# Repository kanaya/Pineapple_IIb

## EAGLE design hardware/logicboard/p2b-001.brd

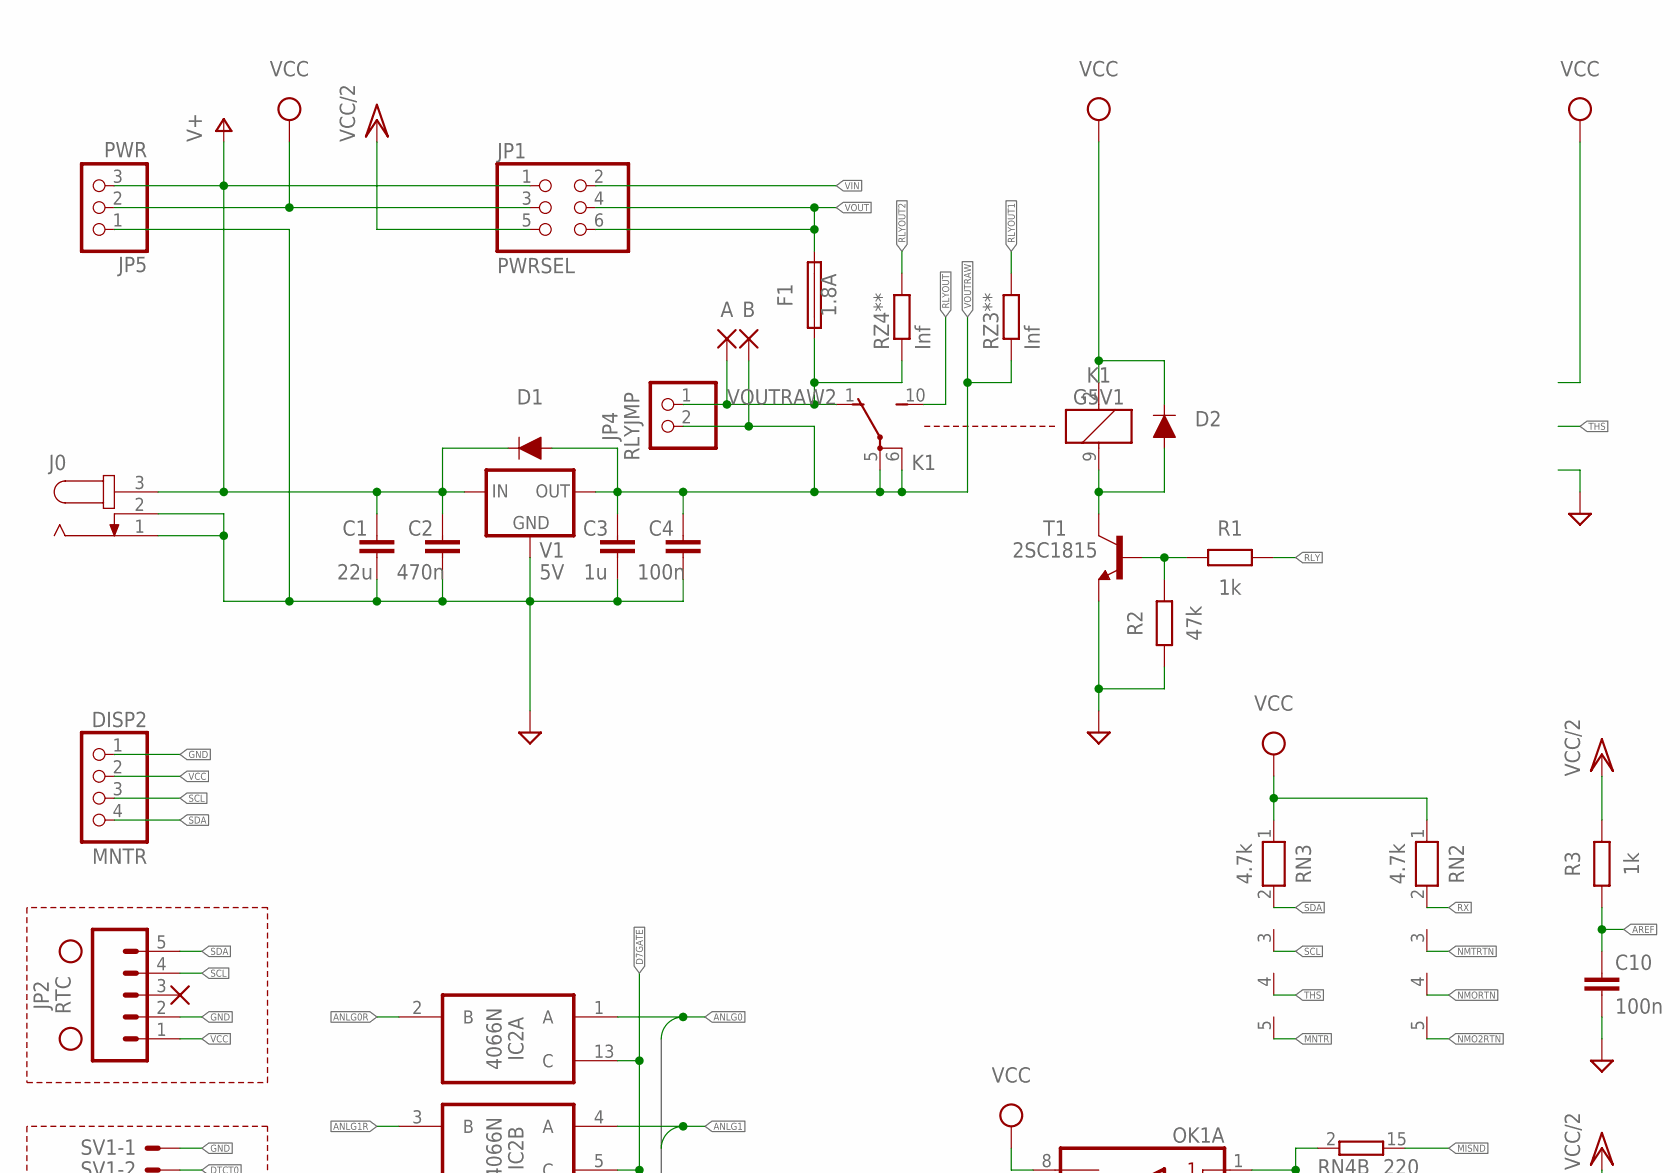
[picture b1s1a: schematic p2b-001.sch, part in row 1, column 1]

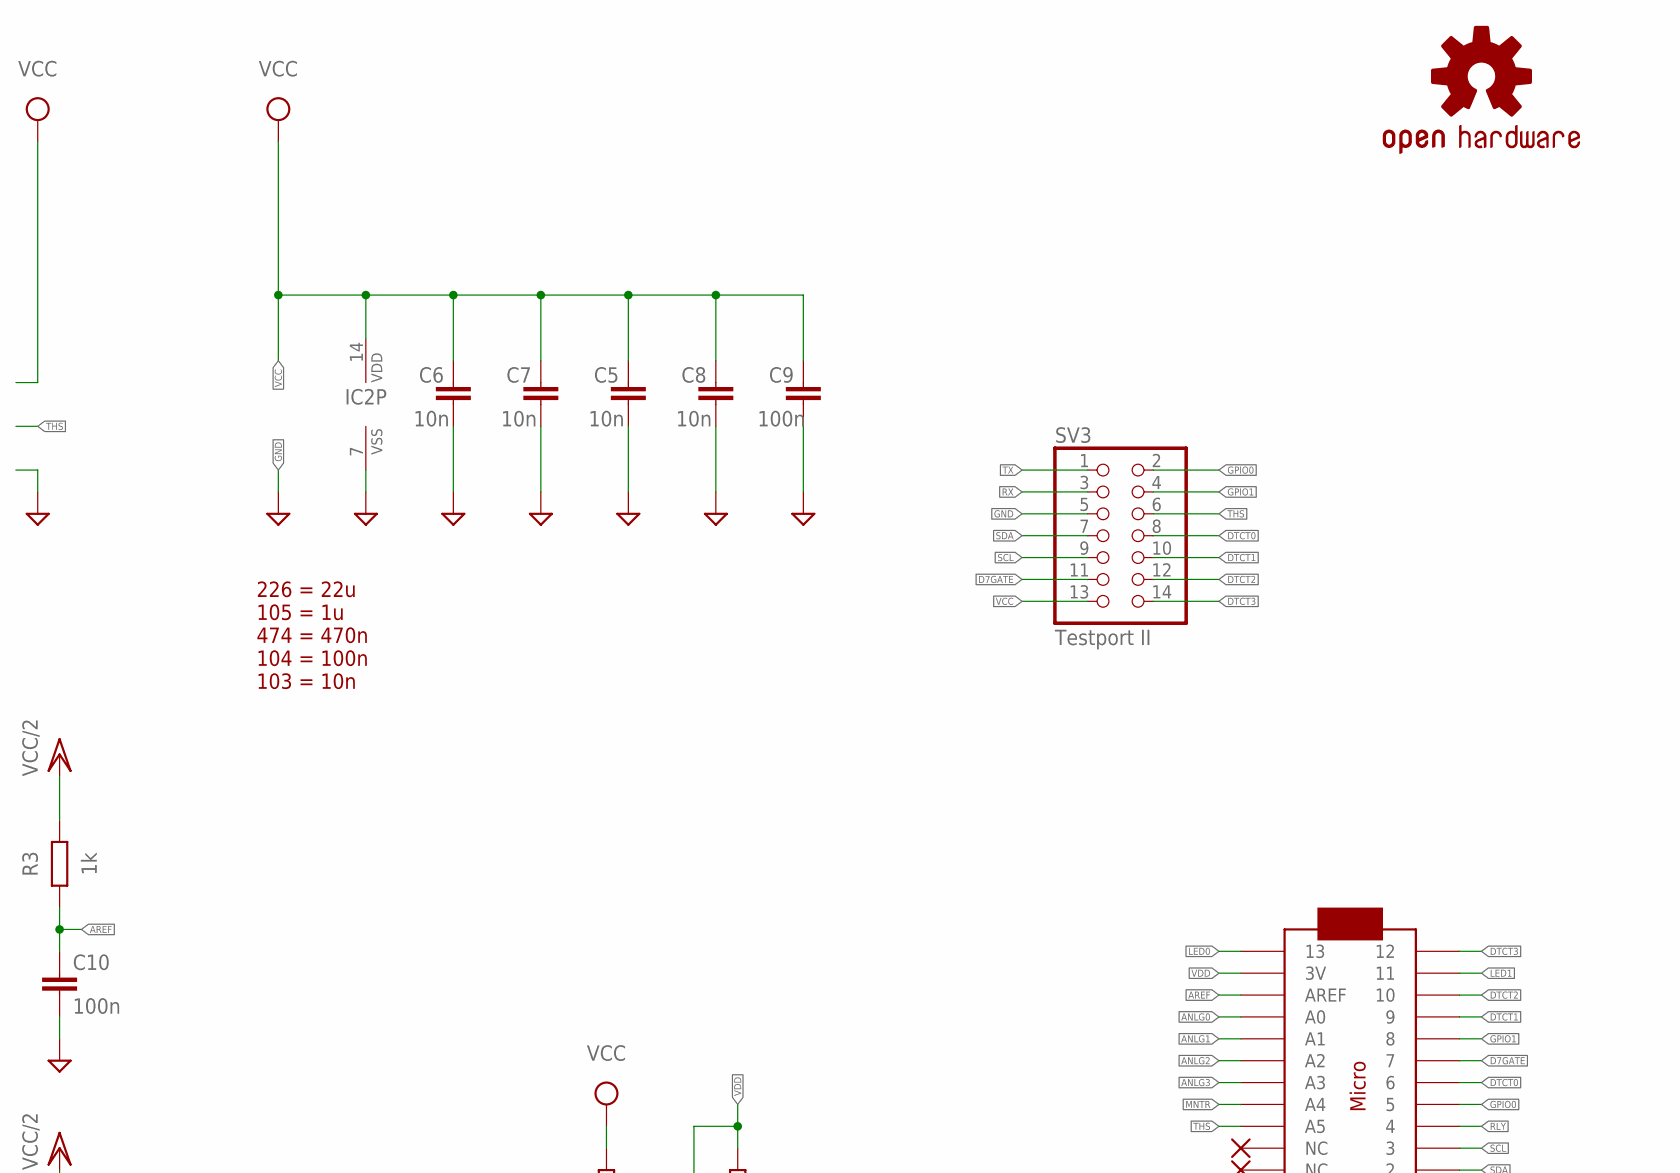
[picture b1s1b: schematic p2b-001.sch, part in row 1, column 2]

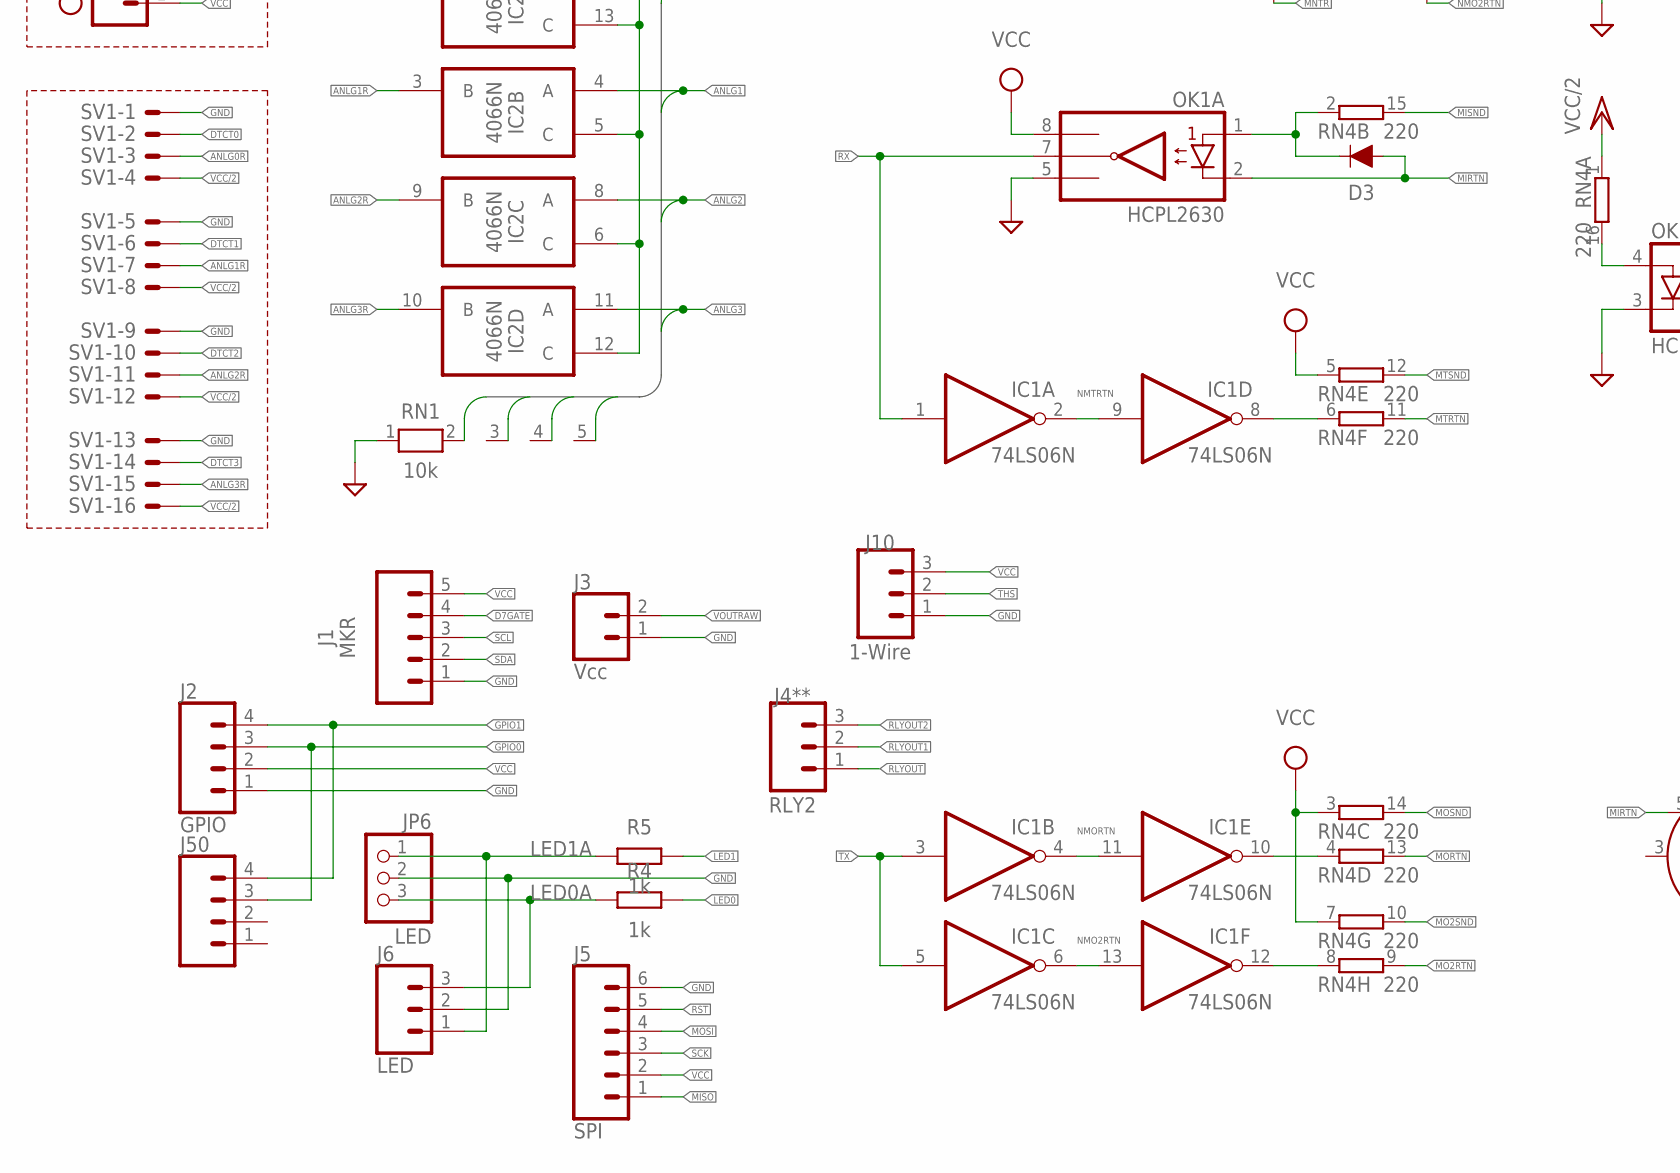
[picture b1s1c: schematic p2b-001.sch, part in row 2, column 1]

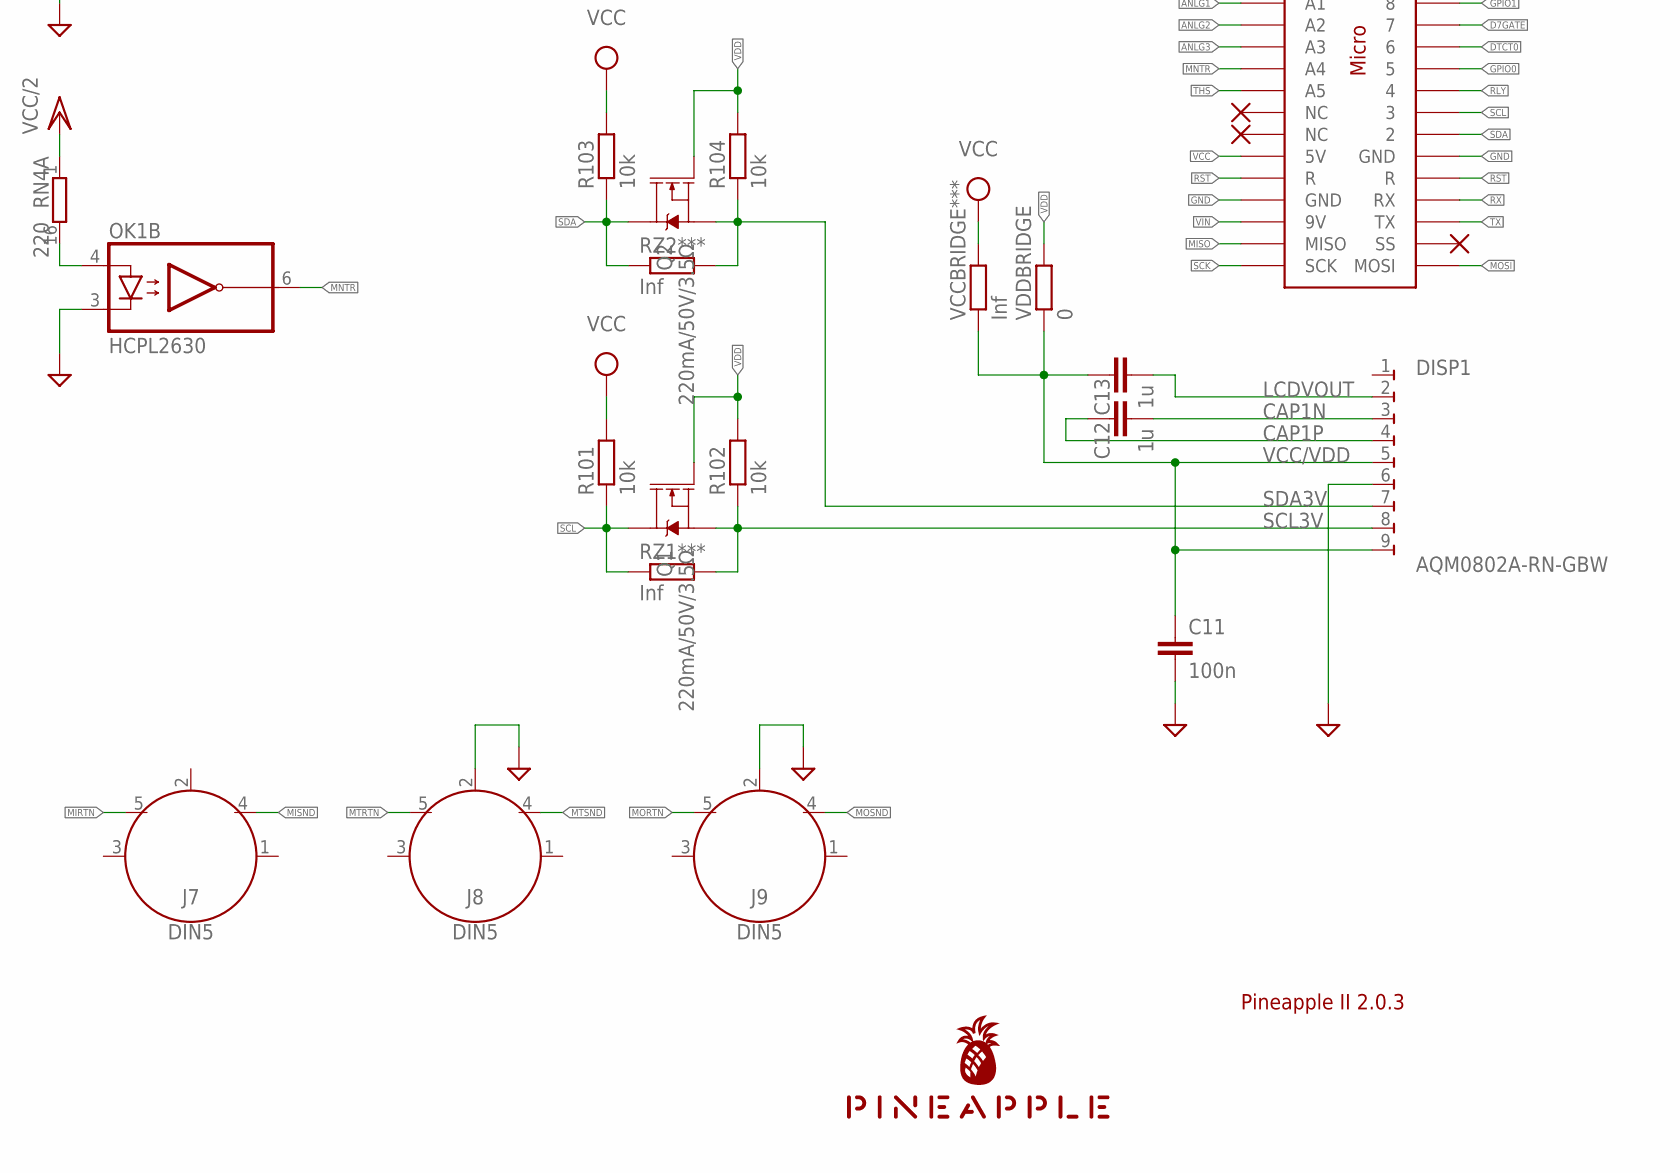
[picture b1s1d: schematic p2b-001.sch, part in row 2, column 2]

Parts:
A: SMD2; SMD1,27-2,54
B: SMD2; SMD1,27-2,54
C1: 22u; C025-050X050
C2: 470n; C050-024X044
C3, C12, C13: 1u; C050-024X044
C4, C9, C10, C11: 100n; C025-024X044
C5, C6, C7, C8: 10n; C025-024X044
D1, D2, D3: DIODE-1N4148
DISP1: AQM0802A-RN-GBW; AQM0802A-RN-GBW-FOOTPRINT
DISP2: MNTR; 1X04
F1: 1.8A; TE5
H1, H2: STAND-OFF
IC1: 74LS06N; DIL14
IC2: 4066N; DIL14
J0: JACK-PLUG0; SPC4077
J1: MKR; JST-5-PTH
J2: GPIO; JST-4-PTH
J3: Vcc; JST-2-PTH
J4**: RLY2; JST-3-PTH-NS
J5: SPI; 1X06_1.27MM
J6: LED; JST-3-PTH-VERT
J7, J8, J9: DIN5; DIN5-RA-PTH
J10: 1-Wire; JST-3-PTH-VERT
J50: CONN_041.27MM; 1X04_1.27MM
JP1: PWRSEL; 2X03
JP2: RTC; 1X05
JP4: RLYJMP; 1X02
JP5: PWR; 1X03
JP6: LED; 1X03
K1: G5V1
LOGO1: OSHW-LOGOS-COPPER; OSHW-LOGO-S_COPPER
MC1: ARDUINOMICRO
OK1: HCPL2630; DIL08
Q1, Q2: 220mA/50V/3.5Ω; SOT23-3
R1, R3, R4, R5: 1k; 0204/5
R2: 47k; 0204/5
R101, R102, R103, R104: 10k; M2012
RN1: 10k; RN-5
RN2, RN3: 4.7k; RN-5
RN4: 220; DIL16
RZ1***, RZ2***, RZ3**, RZ4**: Inf; M2012
SV1: ML16LE; ML16L
SV3: Testport II; 2X07
T1: 2SC1815; TO92-ECB
U$1: PINEAPPLE450_SILK
V1: 5V; 78XXL
VCCBRIDGE***: Inf; M2012
VDDBRIDGE: 0; M2012

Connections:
ANLG0: IC2.1 (A), MC1.P$31 (A0), RN1.2
ANLG0R: IC2.2 (B), SV1.3
ANLG1: IC2.4 (A), MC1.P$30 (A1), RN1.3
ANLG1R: IC2.3 (B), SV1.7
ANLG2: IC2.8 (A), MC1.P$29 (A2), RN1.4
ANLG2R: IC2.9 (B), SV1.11
ANLG3: IC2.11 (A), MC1.P$28 (A3), RN1.5
ANLG3R: IC2.10 (B), SV1.15
AREF: C10.1, MC1.P$32 (AREF), R3.1
CAP1N: C12.2, DISP1.3
CAP1P: C12.1, DISP1.4
D7GATE: IC2.5 (C), IC2.6 (C), IC2.12 (C), IC2.13 (C), J1.4, MC1.P$6 (7), SV3.11
DTCT0: MC1.P$7 (6), SV1.2, SV3.8
DTCT1: MC1.P$4 (9), SV1.6, SV3.10
DTCT2: MC1.P$3 (10), SV1.10, SV3.12
DTCT3: MC1.P$1 (12), SV1.14, SV3.14
GND: C1.2, C2.2, C3.2, C4.2, C5.2, C6.2, C7.2, C8.2, C9.2, C10.2, C11.2, DISP1.6, DISP2.1, IC1.7 (GND), IC2.7 (VSS), J0.1, J0.2, J1.1, J2.1, J3.1, J5.6, J6.2, J8.2, J9.2, J10.1, JP2.2, JP5.1, JP6.2, MC1.P$12 (GND), MC1.P$21 (GND), OK1.3 (C2), OK1.5 (GND), R2.1, RN1.1, SV1.1, SV1.5, SV1.9, SV1.13, SV3.5, T1.E, V1.GND
GPIO0: J2.3, J50.3, MC1.P$8 (5), SV3.2; also elsewhere on the board
GPIO1: J2.4, J50.4, MC1.P$5 (8), SV3.4; also elsewhere on the board
LCDVOUT: C13.2, DISP1.2
LED0: MC1.P$34 (13), R4.2
LED0A: J6.3, JP6.3, R4.1
LED1: MC1.P$2 (11), R5.2
LED1A: J6.1, JP6.1, R5.1
MIDIINSND: D3.C, OK1.1 (A1), RN4.2 (1)
MIRTN: D3.A, J7.5, OK1.2 (C1)
MISND: J7.4, RN4.15 (2)
MISO: J5.1, MC1.P$19 (MISO)
MNTR: MC1.P$27 (A4), OK1.6 (VO2), RN3.5
MNTRA: OK1.4 (A2), RN4.16 (2)
MO2RTN: RN4.9 (2)
MO2RTNRAW: IC1.12 (O), RN4.8 (1)
MO2SND: RN4.10 (2)
MORTN: J9.5, RN4.13 (2)
MORTNRAW: IC1.10 (O), RN4.4 (1)
MOSI: J5.4, MC1.P$17 (MOSI)
MOSND: J9.4, RN4.14 (2)
MTRTN: J8.5, RN4.11 (2)
MTRTNRAW: IC1.8 (O), RN4.6 (1)
MTSND: J8.4, RN4.12 (2)
NMO2RTN: IC1.6 (O), IC1.13 (I), RN2.5
NMORTN: IC1.4 (O), IC1.11 (I), RN2.4
NMTRTN: IC1.2 (O), IC1.9 (I), RN2.3
RLY: MC1.P$9 (4), R1.2
RLYDRV: R1.1, R2.2, T1.B
RLYOUT: J4**.1, K1.10 (S)
RLYOUT1: J4**.2, RZ3**.2
RLYOUT2: J4**.3, RZ4**.2
RLYSNK: D2.A, K1.9 (2), T1.C
RST: J5.5, MC1.P$13 (R), MC1.P$22 (R)
RX: IC1.1 (I), MC1.P$14 (RX), OK1.7 (VO1), RN2.2, SV3.3
SCK: J5.3, MC1.P$18 (SCK)
SCL: DISP2.3, J1.3, JP2.4, MC1.P$10 (3), Q1.3 (D), R101.1, RN3.3, RZ1***.1, SV3.9
SCL3V: DISP1.8, Q1.2 (S), R102.1, RZ1***.2
SDA: DISP2.4, J1.2, JP2.5, MC1.P$11 (2), Q2.3 (D), R103.1, RN3.2, RZ2***.1, SV3.7
SDA3V: DISP1.7, Q2.2 (S), R104.1, RZ2***.2
THS: J10.2, MC1.P$26 (A5), RN3.4, SV3.6
TX: IC1.3 (I), IC1.5 (I), MC1.P$15 (TX), SV3.1
V+: C1.1, C2.1, D1.C, J0.3, JP1.1, JP5.3, V1.IN
VCC: C5.1, C6.1, C7.1, C8.1, C9.1, D2.C, DISP2.2, IC1.14 (VCC), IC2.14 (VDD), J1.5, J2.2, J5.2, J10.3, JP1.3, JP2.1, JP5.2, K1.2 (1), MC1.P$23 (5V), OK1.8 (VCC), R101.2, R103.2, RN2.1, RN3.1, RN4.3 (1), RN4.5 (1), RN4.7 (1), SV3.13, VCCBRIDGE***.2
VCC/2: JP1.5, R3.2, RN4.1, SV1.4, SV1.8, SV1.12, SV1.16
VCC/VDD: C11.1, C13.1, DISP1.5, DISP1.9, VCCBRIDGE***.1, VDDBRIDGE.1
VDD: MC1.P$33 (3V), Q1.1 (G), Q2.1 (G), R102.2, R104.2, VDDBRIDGE.2
VIN: JP1.2, MC1.P$20 (9V)
VOUT: F1.2, JP1.4, JP1.6
VOUTRAW: B.1, C3.1, C4.1, D1.A, J3.2, JP4.2, K1.5, K1.6, RZ3**.1, V1.OUT
VOUTRAW2: A.1, F1.1, JP4.1, K1.1 (O), RZ4**.1

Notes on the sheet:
Pineapple II 2.0.3
226 = 22u 105 = 1u 474 = 470n 104 = 100n 103 = 10n

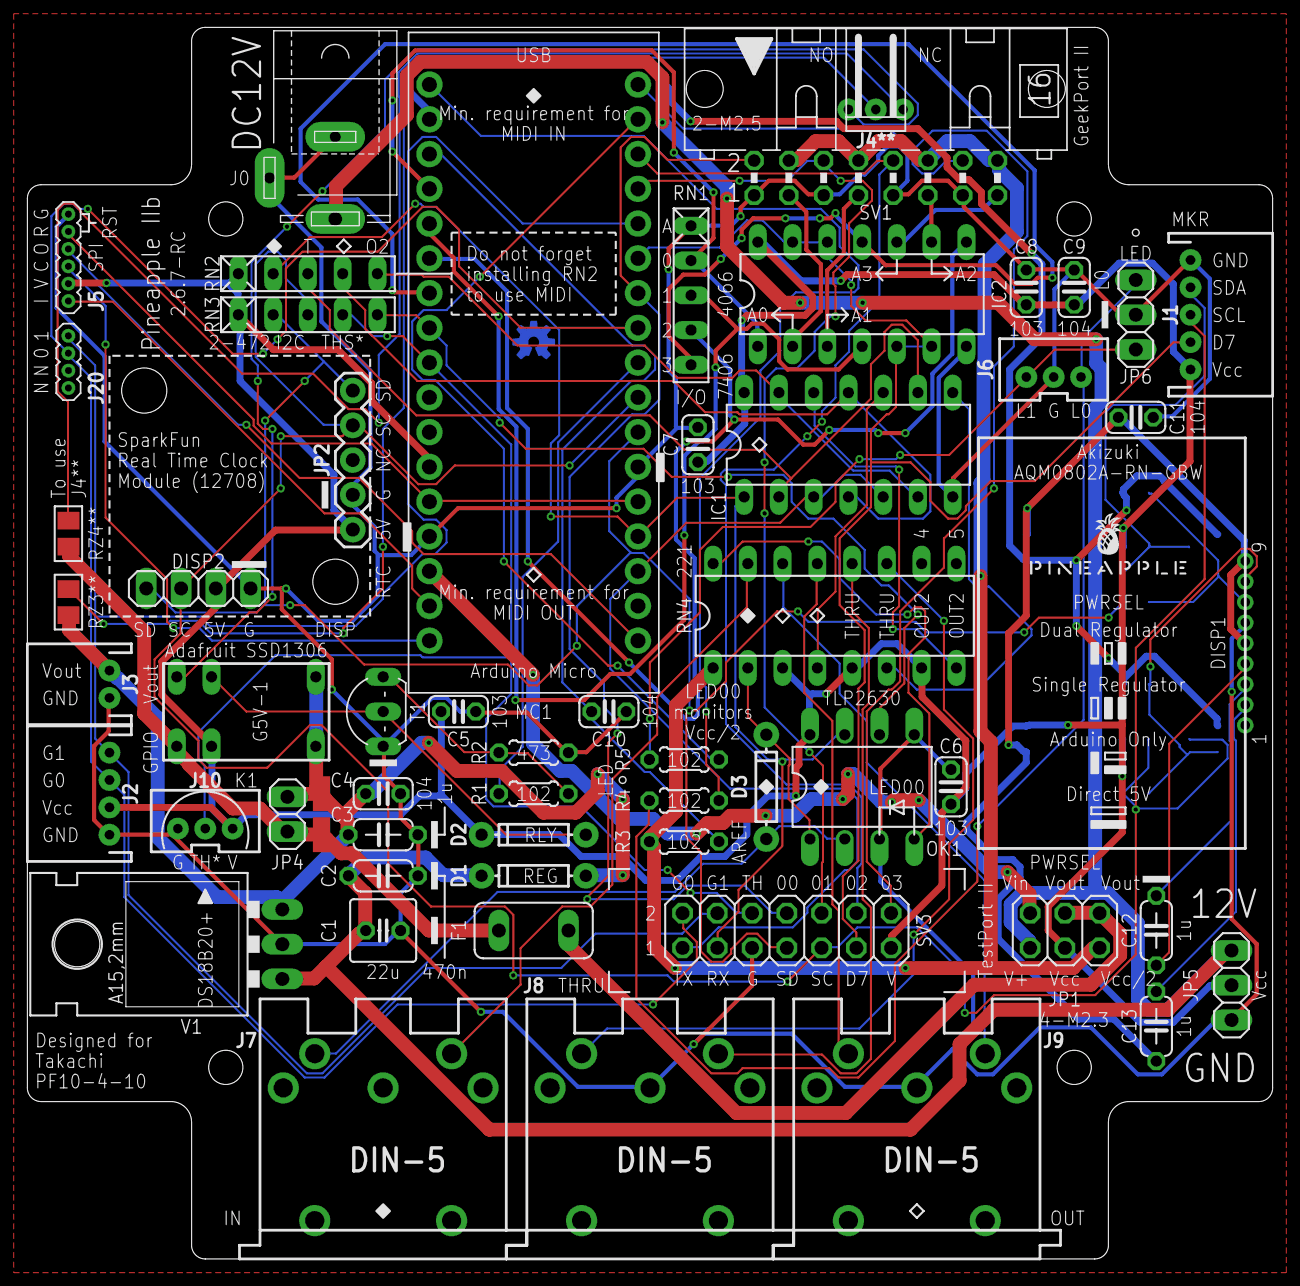
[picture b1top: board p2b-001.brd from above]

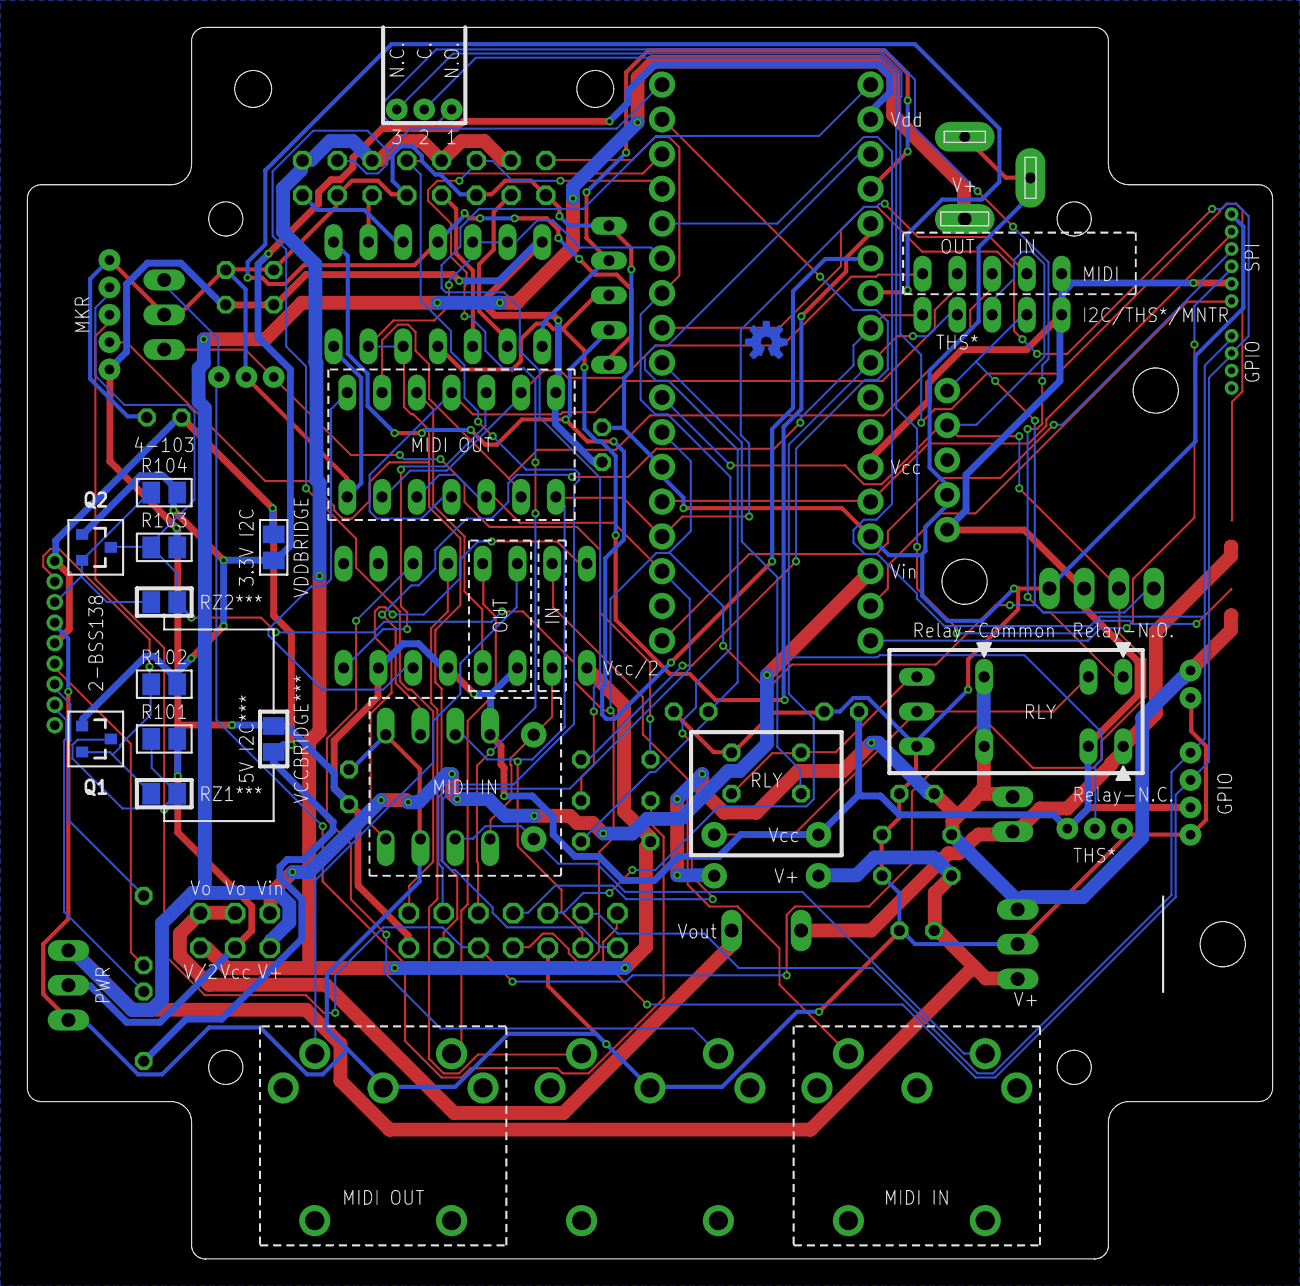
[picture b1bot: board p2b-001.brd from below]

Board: 2 copper layers, 91.0 x 90.0 mm, 72 parts (11 on the bottom side), 65 nets.

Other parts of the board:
J20: 1X04_1.27MM

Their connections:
GPIO0: J20.3; also elsewhere on the board
GPIO1: J20.4; also elsewhere on the board

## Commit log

2021-03-29 Imported Pineapple IIb logicboard design from Pineapple II repo.
2021-03-29 Test flight.
2021-03-30 Layout.
2021-03-31 Fine tune.
2021-04-02 Swapped MIDI RX+ and MIDI RX DETECT.
2021-04-04 Test pin.
2021-04-06 Silk.
2021-04-10 Renumbered parts.
2021-04-13 Clean up.
2021-10-31 New back port, broader power pattern.
2021-11-07 LED0->LED1, LED1->LED2.
2021-11-09 Followed Pineapple II 2.4.0 design. Before autorouting.
2021-11-09 Swapped RN1 and RN2.
2021-11-09 The new test pad.
2021-11-10 Rastnet.
2021-11-10 Changed radius of restricted area to 2.25mm.
2021-11-11 Rounded corner.
2021-11-11 Refined restricted pattern.
2021-11-11 Refined (again).
2021-11-12 Fixed outline of the board.
2021-11-12 Relocated R3, R4, R5.
2021-11-12 Added LED00 pattern.
2021-11-24 Renumbered signal names and silk patterns.
2021-11-29 Added silk of LED0/1.
2021-11-29 Added J6 (LED connector).
2021-11-29 Re-arranged GeekPort 2.0.
2021-11-30 Fixed silk.
2021-11-30 Added holes for backport ii.
2021-11-30 Added pogo pins to GeekPort II.
2021-12-01 GND pattern. Fixed drill size.
2021-12-01 TestPort II.
2021-12-01 GND pattern.
2021-12-02 Redesign of TestPort II.
2021-12-11 Fixed silk saying 4-M3.
2021-12-12 Flipped TestPort.
2021-12-12 Moved several parts slightly.
2021-12-13 Changed signal name from RXDTCT to NDX.
2021-12-17 Unflip TestPort.
2021-12-17 Fixed backside silk.
2021-12-17 Added Power Pad.
2021-12-17 Added relay pad.
2021-12-17 Replaced ML connector with header pins.
2021-12-17 Position of Tr.
2021-12-17 Changed silk of BackPort II.
2021-12-29 Fixed silk pattern.
2021-12-29 Moved GeekPort to right 1mm.
2021-12-30 New TestPort II.
2021-12-30 Give some names to unnamed parts.
2022-01-27 Changed corner radiuses.
2022-01-28 Dummy pinholes.
2022-01-28 Size of dummy holes.
2022-01-28 Swapped position of RN2 and RN3.
2022-01-29 Backside silk.
2022-02-02 Trying to add restricted zones.
2022-02-02 Added restricted zones.
2022-02-19 Added JPX, which is to be renamed.
2022-02-19 Finished up OLED con.
2022-02-21 LCD ready.
2022-02-22 Now LCD runs at 5V.
2022-02-22 Signal name.
2022-02-23 Position of LCD.
2022-02-23 Now LCD runs on 5V or 3.3V.
2022-06-08 Fixed silk and signal errors.
2022-08-01 Now has relay terminal as J42.
2022-08-01 3-port relay terminal.
2022-08-01 Autorouted.
2022-08-02 J4 is now 3-pin.
2022-08-02 Fixed SCL signal.
2022-08-02 Moved J4.
2022-08-02 Moved J4 (again).
2022-08-02 Silk. 2.6.1-B to 2.6.1-RC.
2022-08-03 Fixed silk for TLP2630 optocoupler.
2022-08-15 Reset pins.
2022-08-22 Unrouted.
2022-08-22 SPI port. GPIO port. Vcc port.
2022-08-22 Front-side RLY jumper.
2022-08-23 J3 is now Voutraw conn.
2022-08-23 Silk (DC9V -> DC12V).
2022-08-26 Trying to implement 1-Wire port.
2022-08-29 SPI port.
2022-08-29 Autoroute.
2022-08-30 New interface.
2022-08-30 Done.
2022-08-30 Fixed clearance warning.
2022-09-13 J50->J20.

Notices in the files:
parts and their libraries:
SparkFun-DiscreteSemi: Licensing: Creative Commons ShareAlike 4.0 International - https://creativecommons.org/licenses/by-sa/4.0
